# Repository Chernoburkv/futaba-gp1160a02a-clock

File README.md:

# futaba-gp1160a02a-clock
My small VFD clock using futaba display, atmega 328P in DIP and ds3231. ECAD files, Code::Blocks project and fuses (also a picture for trummels) included.

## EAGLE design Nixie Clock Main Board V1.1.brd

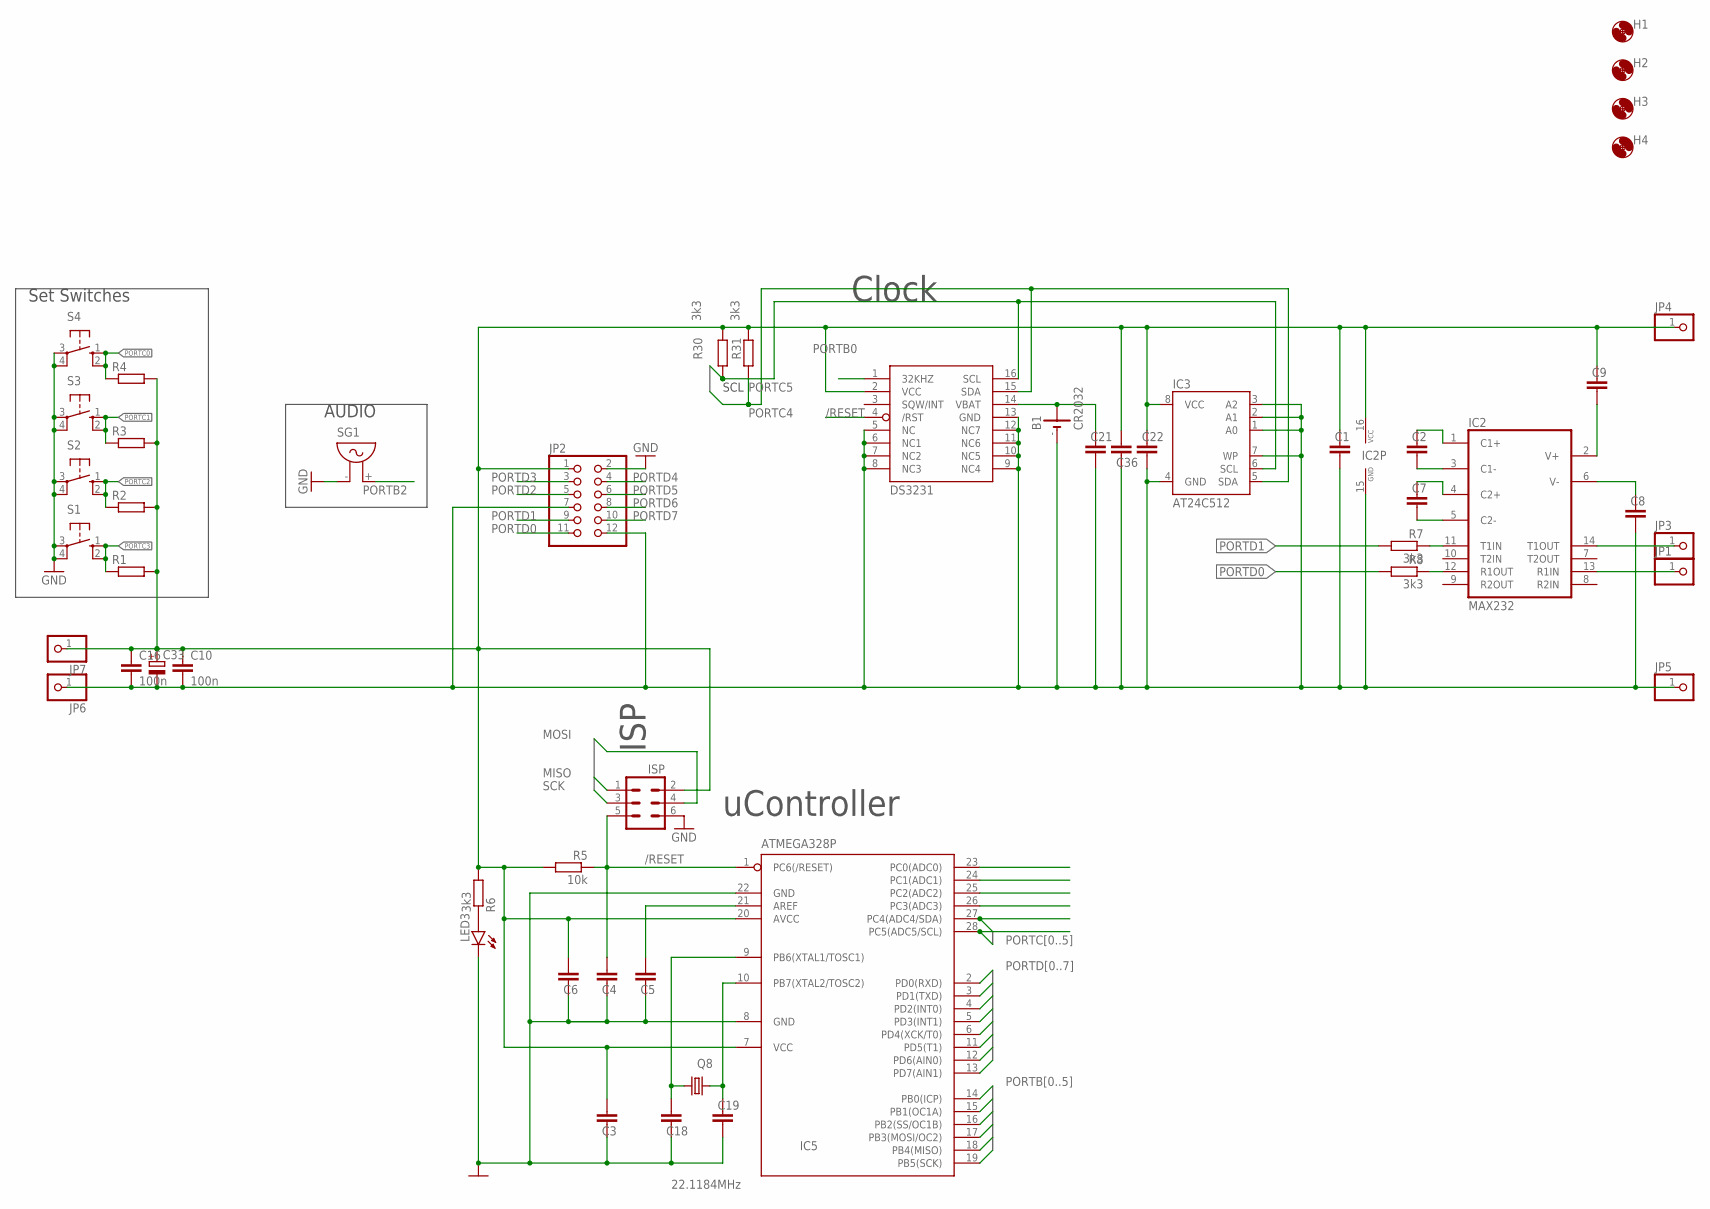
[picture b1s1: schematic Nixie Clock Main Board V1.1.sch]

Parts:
B1: CR2032
C1, C2, C3, C5, C6, C7, C8, C9, C21, C22, C36: C-EUC1206; C1206
C4, C18, C19: C-EUC0805; C0805
C10, C16: 100n; C1206
C33: CPOL-EUE3.5-8; E3,5-8
H1, H2, H3, H4: MOUNT-HOLE3.2; 3,2
IC2: MAX232; DIL16
IC3: AT24C512; DIL08
IC5: ATMEGA328P; DIL28-3
J: ISP; MA03-2
JP1, JP3, JP4, JP5, JP6, JP7: PINHD-1X1; 1X01
JP2: PINHD-2X6; 2X06
LED3: LED5MM
Q8: 22.1184MHz; HC49U-V
R1, R2, R3, R4: R-EU_R0805; R0805
R5: 10k; R0805
R6, R7, R8, R30, R31: 3k3; R0805
S1, S2, S3, S4: 10-XX; B3F-10XX
SG1: F/QMX
U2: DS3231; SO16W

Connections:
+5V: C1.1, C3.1, C6.1, C9.1, C10.1, C16.1, C22.1, C33.+, C36.1, IC2.16 (VCC), IC3.8 (VCC), IC5.7 (VCC), IC5.20 (AVCC), J.2, JP2.1, JP4.1, JP7.1, R1.2, R2.2, R3.2, R4.2, R5.2, R6.2, R30.2, R31.2, U2.2 (VCC)
/RESET: C4.1, IC5.1 (PC6(/RESET)), J.5, R5.1, U2.4 (/RST)
GND: B1.-, C1.2, C3.2, C4.2, C5.2, C6.2, C8.2, C10.2, C16.2, C18.2, C19.2, C21.2, C22.2, C33.-, C36.2, IC2.15 (GND), IC3.1 (A0), IC3.2 (A1), IC3.3 (A2), IC3.4 (GND), IC3.7 (WP), IC5.8 (GND), IC5.22 (GND), J.6, JP2.2, JP2.7, JP2.12, JP5.1, JP6.1, LED3.K (C), S1.3, S1.4 (P1), S2.3, S2.4 (P1), S3.3, S3.4 (P1), S4.3, S4.4 (P1), SG1.- (1), U2.5 (NC), U2.6 (NC1), U2.7 (NC2), U2.8 (NC3), U2.9 (NC4), U2.10 (NC5), U2.11 (NC6), U2.12 (NC7), U2.13 (GND)
MISO: IC5.18 (PB4(MISO)), J.1
MOSI: IC5.17 (PB3(MOSI/OC2)), J.4
unnamed: C7.1, IC2.4 (C2+)
unnamed: C2.2, IC2.3 (C1-)
unnamed: C2.1, IC2.1 (C1+)
unnamed: C7.2, IC2.5 (C2-)
unnamed: C9.2, IC2.2 (V+)
unnamed: C8.1, IC2.6 (V-)
unnamed: IC2.11 (T1IN), R7.1
unnamed: IC2.13 (R1IN), JP1.1
unnamed: IC2.12 (R1OUT), R8.1
unnamed: IC2.14 (T1OUT), JP3.1
unnamed: LED3.A, R6.1
unnamed: C18.1, IC5.9 (PB6(XTAL1/TOSC1)), Q8.1
unnamed: C19.1, IC5.10 (PB7(XTAL2/TOSC2)), Q8.2
unnamed: B1.+, C21.1, U2.14 (VBAT)
unnamed: C5.1, IC5.21 (AREF)
PORTB0: IC5.14 (PB0(ICP)), U2.1 (32KHZ)
PORTB1: IC5.15 (PB1(OC1A))
PORTB2: IC5.16 (PB2(SS/OC1B)), SG1.+ (2)
PORTC0: IC5.23 (PC0(ADC0)), R4.1, S4.1 (S), S4.2 (S1)
PORTC1: IC5.24 (PC1(ADC1)), R3.1, S3.1 (S), S3.2 (S1)
PORTC2: IC5.25 (PC2(ADC2)), R2.1, S2.1 (S), S2.2 (S1)
PORTC3: IC5.26 (PC3(ADC3)), R1.1, S1.1 (S), S1.2 (S1)
PORTC4: IC3.5 (SDA), IC5.27 (PC4(ADC4/SDA)), R31.1, U2.15 (SDA)
PORTC5: IC3.6 (SCL), IC5.28 (PC5(ADC5/SCL)), R30.1, U2.16 (SCL)
PORTD0: IC5.2 (PD0(RXD)), JP2.11, R8.2
PORTD1: IC5.3 (PD1(TXD)), JP2.9, R7.2
PORTD2: IC5.4 (PD2(INT0)), JP2.5
PORTD3: IC5.5 (PD3(INT1)), JP2.3
PORTD4: IC5.6 (PD4(XCK/T0)), JP2.4
PORTD5: IC5.11 (PD5(T1)), JP2.6
PORTD6: IC5.12 (PD6(AIN0)), JP2.8
PORTD7: IC5.13 (PD7(AIN1)), JP2.10
SCK: IC5.19 (PB5(SCK)), J.3

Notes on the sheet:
Set Switches
AUDIO
Clock
uController
SCL
ISP

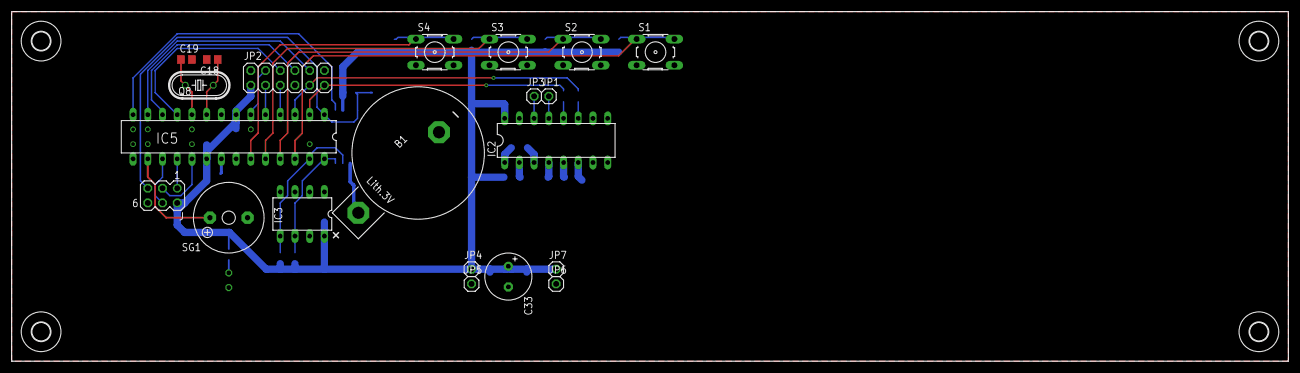
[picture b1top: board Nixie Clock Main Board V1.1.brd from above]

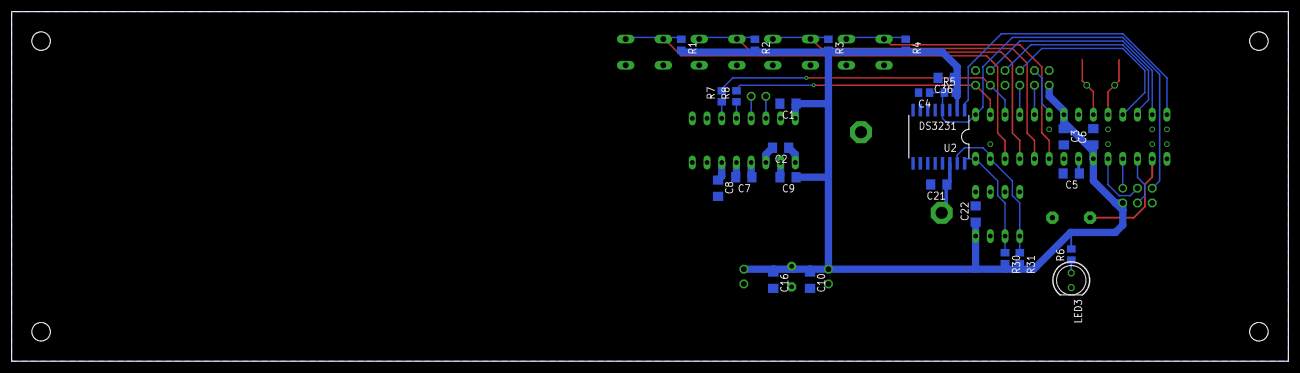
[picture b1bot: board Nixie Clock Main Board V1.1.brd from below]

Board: 2 copper layers, 220.3 x 60.3 mm, 51 parts (26 on the bottom side), 37 nets.

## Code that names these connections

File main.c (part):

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#define BUTTON_REGISTER DDRC
#define BUTTON_PIN PINC

#define B0 (1 << PC0)    //0
#define B1 (1 << PC1)    //1
#define B2 (1 << PC2)    //2
#define B3 (1 << PC3)    //3

void uart_send(uint8_t * data, uint16_t len);
void uart_print(char * str);
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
